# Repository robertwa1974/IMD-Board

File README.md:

# DIY insulation monitor (IMD) for EV conversions

An insulation monitoring device for DIY EV conversions. It measures the insulation resistance from
HV+ and HV- to chassis using a switched-resistor bridge, and has Bender IR155-compatible outputs
(MHS PWM + OKHS). It stacks on the contactor economizer board, or runs stand-alone with one 12-pin harness plug
(power, MHS/OKHS, optional contactor and inhibit inputs, UART): see DESIGN_NOTES "Stand-alone use".

**Status:** rev A first pass: schematic, routed 110 x 66 mm PCB (JLCPCB outputs in `hw/fab/`), firmware core host-tested. Nothing built or run on hardware yet. DIY and uncertified: not a substitute for a
certified IMD in a product.

| Path | What |
|---|---|
| `HANDOFF.md` | Requirements, measurement method, economizer interface |
| `DESIGN_NOTES.md` | Part choices, calculations, PCB rules, open items |
| `hw/` | KiCad 10 schematic generated from `hw/design.py` (`imd_schematic.pdf` to view) |
| `src/imd/`, `lib/imd_core/` | IMD board firmware (STM32G031) and its host-testable core |
| `lib/ir155_decoder/`, `src/m5dial/` | IR155 MHS decoder for an M5Dial (ESP32-S3) |
| `test/` | Host unit tests: decoder, bridge maths, state machine vs. a simulated vehicle, UART frames |
| `BENCH_TEST.md` | Bench test of the IMD firmware on a Nucleo-G031K8 with a scaled low-voltage bridge (no HV) |

```
pio run -e imd             # IMD firmware (bench: Nucleo-G031K8, upload with -t upload)
pio run -e m5dial          # decoder for the M5Dial
pio test -e native         # host tests; needs gcc/g++ on PATH, e.g. MSYS2:
                           #   PATH=/c/msys64/mingw64/bin:$PATH pio test -e native
```

MIT licensed. See `LICENSE`.

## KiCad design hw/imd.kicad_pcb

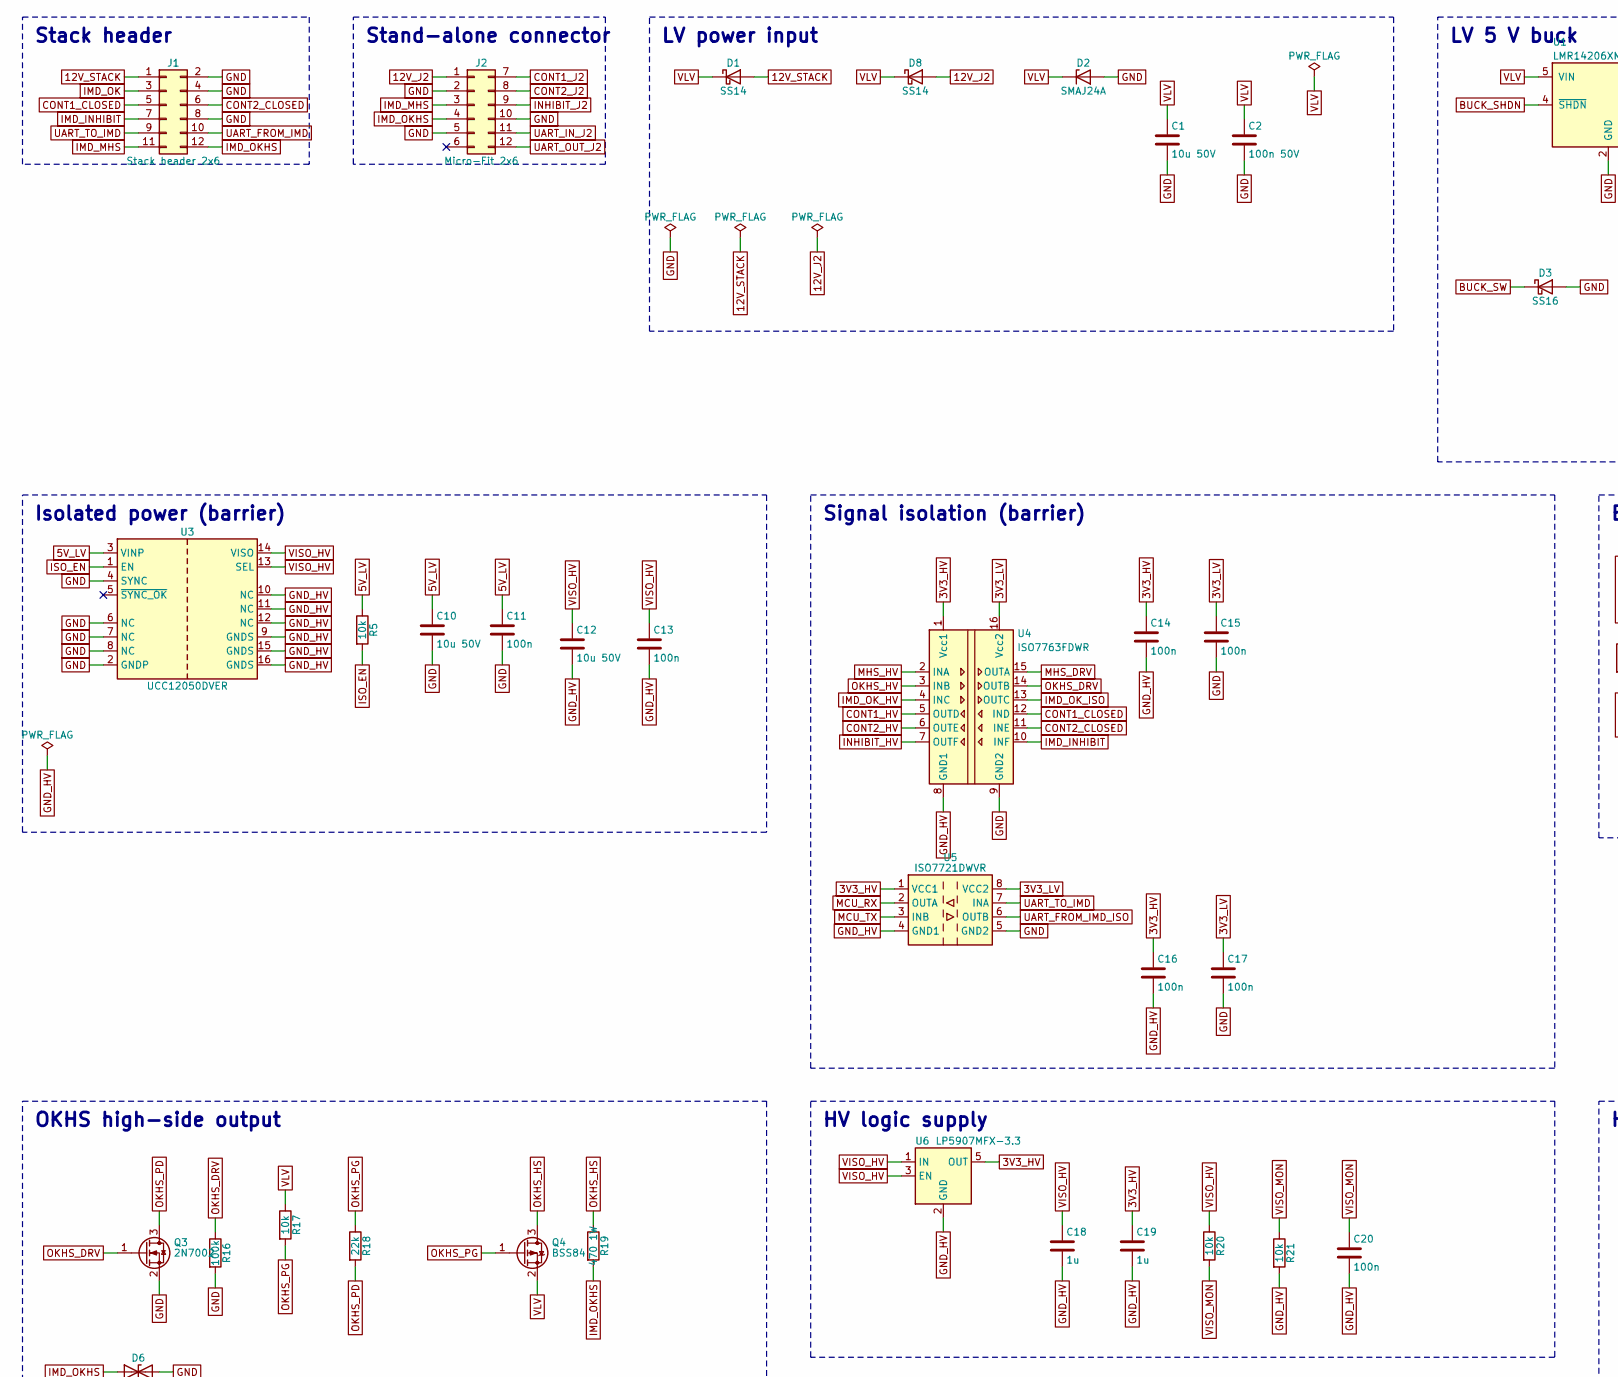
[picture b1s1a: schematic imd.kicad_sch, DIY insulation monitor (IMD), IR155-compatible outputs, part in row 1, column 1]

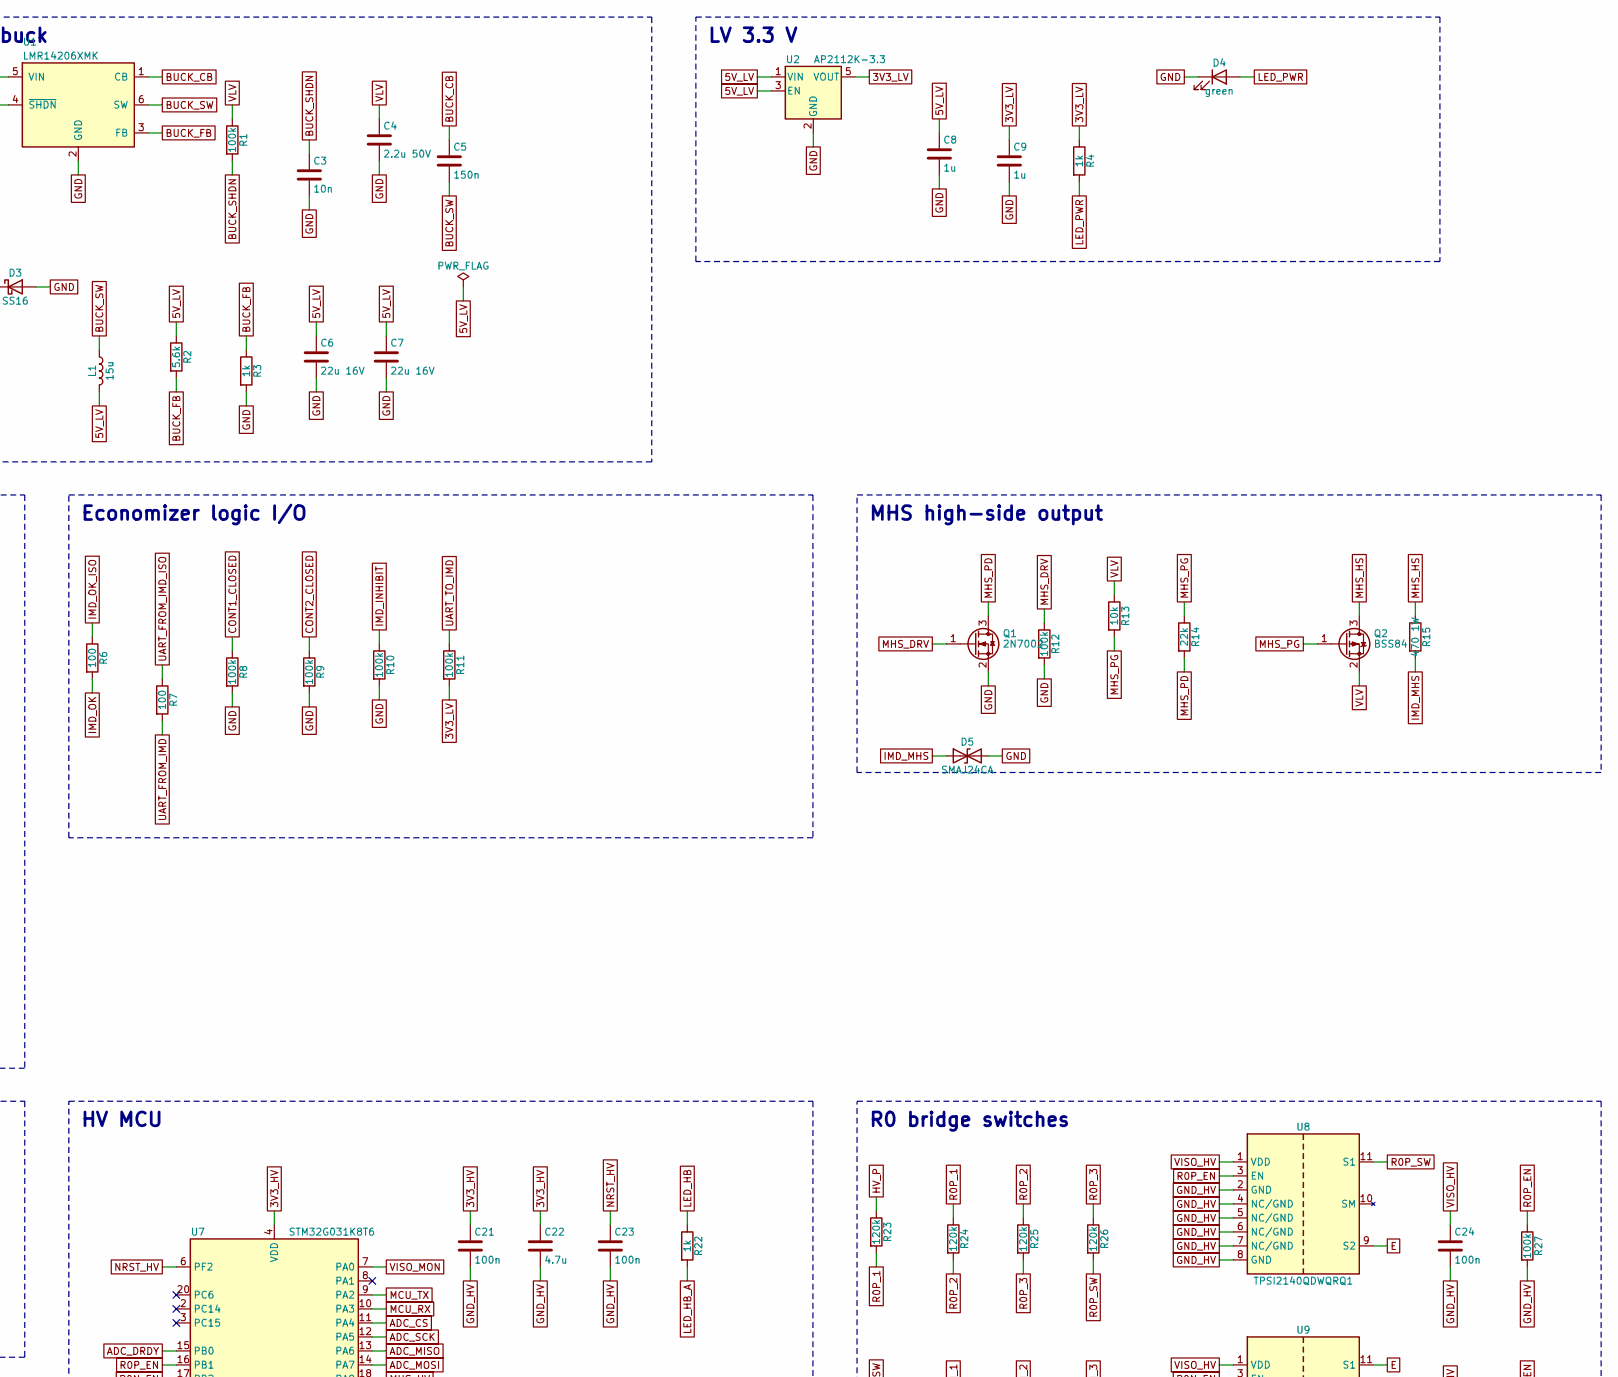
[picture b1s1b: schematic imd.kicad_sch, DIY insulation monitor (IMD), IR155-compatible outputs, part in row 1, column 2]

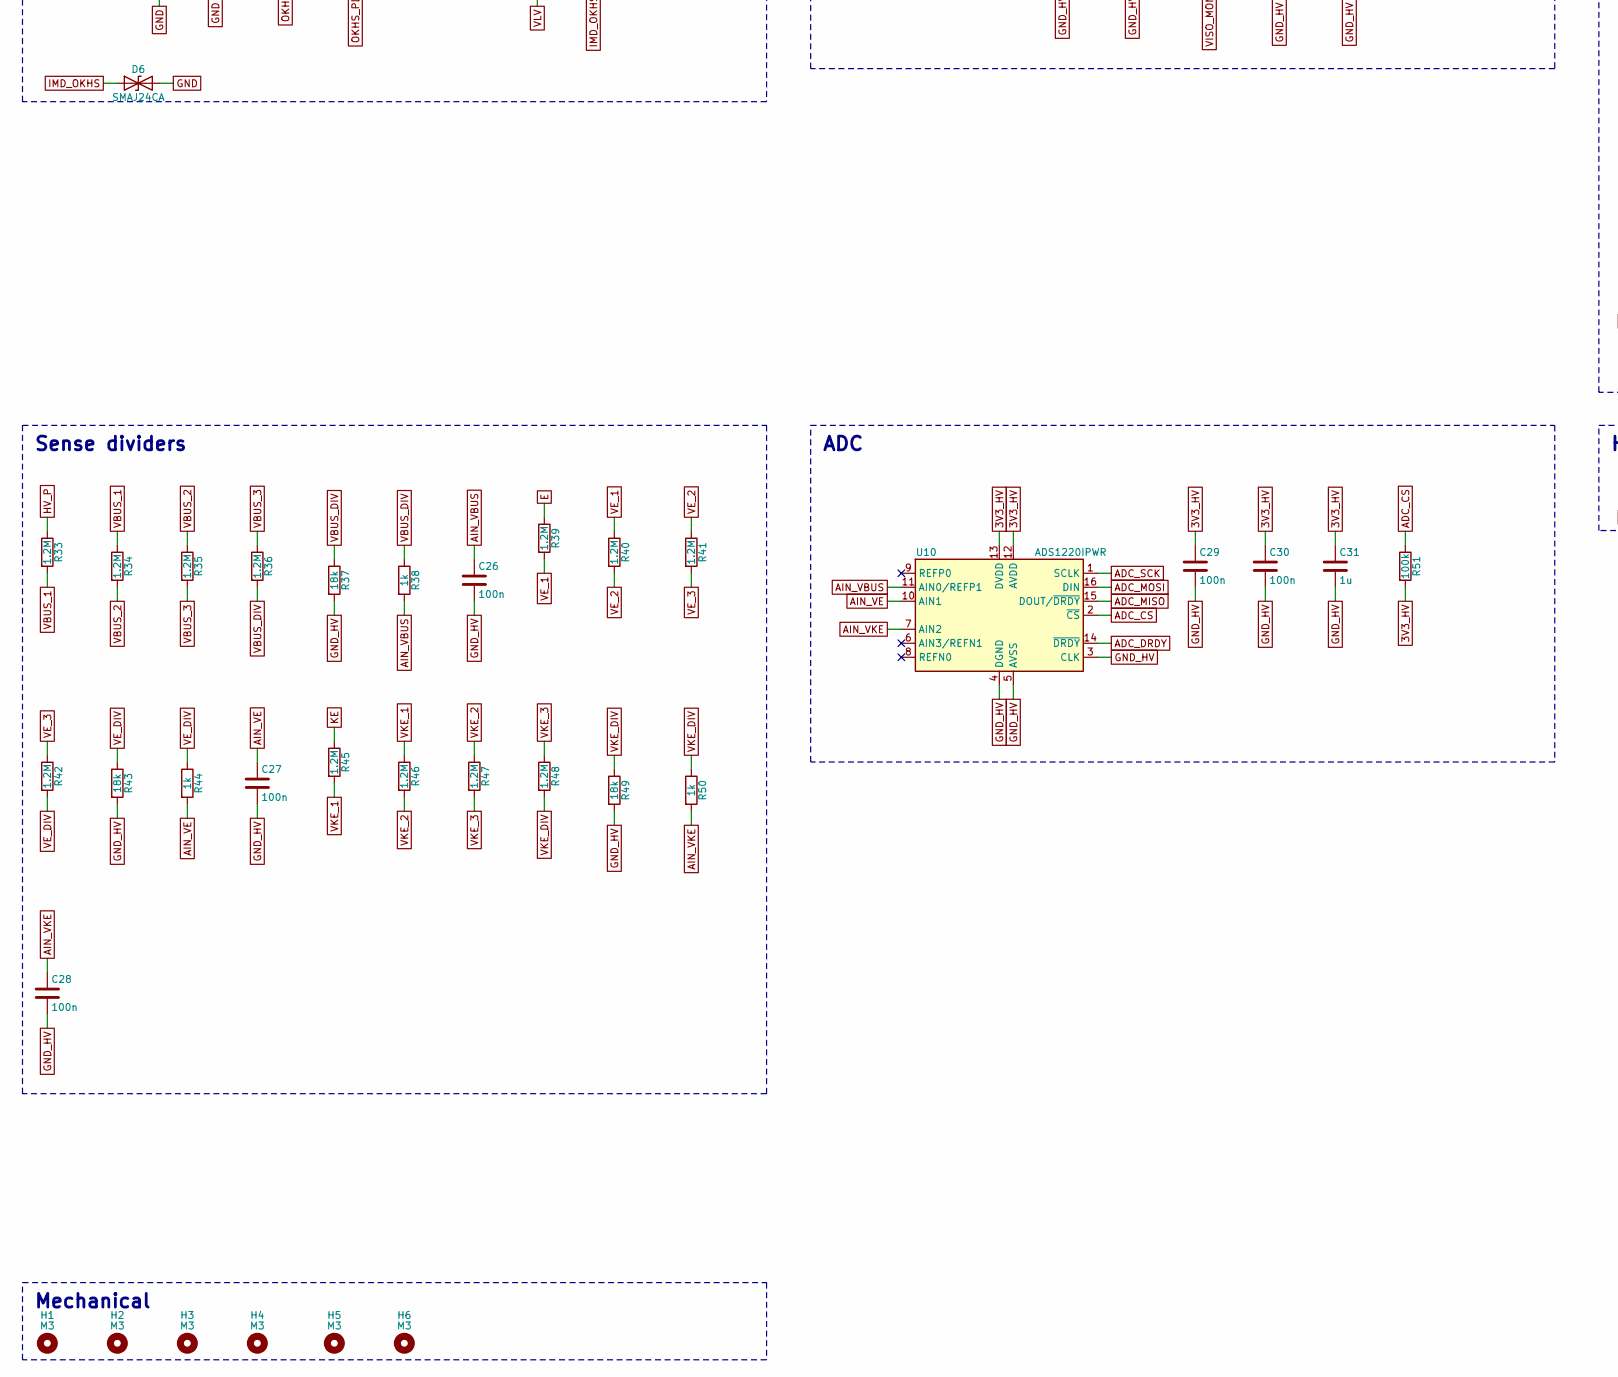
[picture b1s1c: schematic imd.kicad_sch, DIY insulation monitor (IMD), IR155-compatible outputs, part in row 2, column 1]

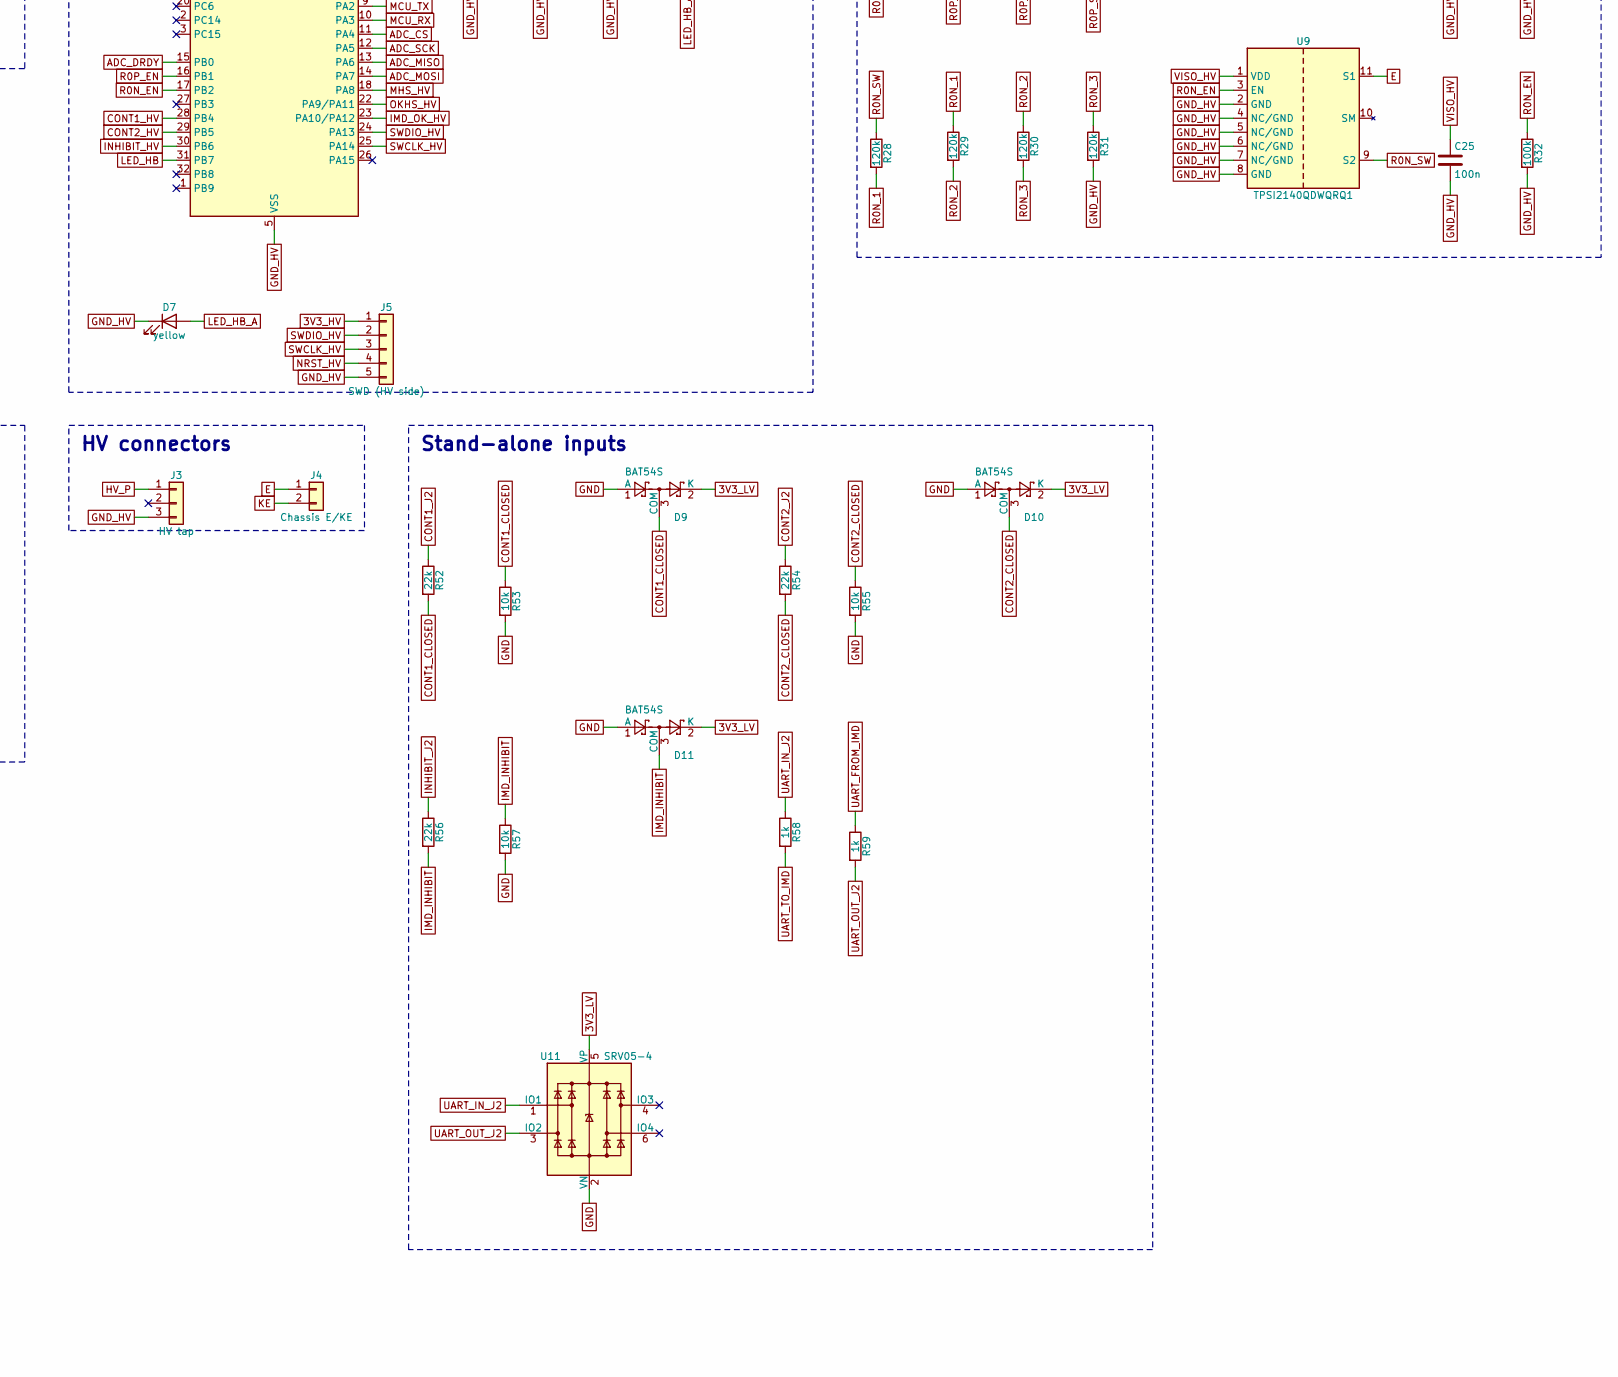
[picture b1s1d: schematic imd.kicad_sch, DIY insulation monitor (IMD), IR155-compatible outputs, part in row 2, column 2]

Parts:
C1, C10, C12: 10u 50V; C_1206_3216Metric; LCSC C13585
C2: 100n 50V; C_0603_1608Metric; LCSC C14663
C3: 10n; C_0603_1608Metric; LCSC C57112
C4: 2.2u 50V; C_1206_3216Metric; LCSC C50254
C5: 150n; C_0603_1608Metric; LCSC C282674
C6, C7: 22u 16V; C_1206_3216Metric; LCSC C12891
C8, C9, C18, C19, C31: 1u; C_0603_1608Metric; LCSC C15849
C11, C13, C14, C15, C16, C17, C20, C21, C23, C24, C25, C26, C27, C28, C29, C30: 100n; C_0603_1608Metric; LCSC C14663
C22: 4.7u; C_0603_1608Metric; LCSC C19666
D1, D8: SS14; D_SMA; MPN SS14; LCSC C2480
D2: SMAJ24A; D_SMA; MPN SMAJ24A (unidirectional TVS); LCSC C3001960
D3: SS16; D_SMA; MPN SS16; LCSC C2481
D4: green; LED_0603_1608Metric; LCSC C72043
D5, D6: SMAJ24CA; D_SMA; MPN SMAJ24CA (bidirectional); LCSC C113963
D7: yellow; LED_0603_1608Metric; LCSC C72038
D9, D10, D11: BAT54S; SOT-23; MPN BAT54S; LCSC C171786
H1, H2, H3, H4, H5, H6: M3; MountingHole_3.2mm_M3
J1: Stack header 2x6; PinHeader_2x06_P2.54mm_Vertical; MPN 2x6 elevated male header, 2.54 mm (leng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
J2: Micro-Fit 2x6; Molex_Micro-Fit_3.0_43045-1200_2x06_P3.00mm_Horizontal; MPN Molex 43045-1200; LCSC C277636
J3: HV tap; Molex_Micro-Fit_3.0_43650-0300_1x03_P3.00mm_Horizontal; MPN Molex 43650-0300; LCSC C503478
J4: Chassis E/KE; Molex_Micro-Fit_3.0_43650-0200_1x02_P3.00mm_Horizontal; MPN Molex 43650-0200 (not at LCSC: Digi-Key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
J5: SWD (HV side); PinHeader_1x05_P2.54mm_Vertical
L1: 15u; L_Bourns_SRN6045TA; MPN Bourns SRN6045-150M; LCSC C3224592
Q1, Q3: 2N7002; SOT-23; MPN 2N7002; LCSC C8545
Q2, Q4: BSS84; SOT-23; MPN LBSS84LT1G; LCSC C8492
R1, R8, R9, R10, R11, R12, R16, R27, R32, R51: 100k; R_0603_1608Metric; LCSC C25803
R2: 5.6k; R_0603_1608Metric; LCSC C23189
R3, R4, R22, R38, R44, R50, R58, R59: 1k; R_0603_1608Metric; LCSC C21190
R5, R13, R17, R20, R21, R53, R55, R57: 10k; R_0603_1608Metric; LCSC C25804
R6, R7: 100; R_0603_1608Metric; LCSC C22775
R14, R18, R52, R54, R56: 22k; R_0603_1608Metric; LCSC C31850
R15, R19: 470 1W; R_2512_6332Metric; LCSC C351718
R23, R24, R25, R26, R28, R29, R30, R31: 120k; R_1206_3216Metric; MPN 1206 thick film 1 %, 200 V rated (112 V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; LCSC C17908
R33, R34, R35, R36, R39, R40, R41, R42, R45, R46, R47, R48: 1.2M; R_1206_3216Metric; MPN 1206 thick film 1 %, 200 V rated (112 V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; LCSC C22107
R37, R43, R49: 18k; R_0603_1608Metric; LCSC C25810
U1: LMR14206XMK; TSOT-23-6; MPN LMR14206XMKE/NOPB; LCSC C2071127
U2: AP2112K-3.3; SOT-23-5; MPN AP2112K-3.3TRG1; LCSC C51118
U3: UCC12050DVER; SOIC-16W_7.5x10.3mm_P1.27mm; MPN UCC12050DVER (UCC12051QDVERQ1 automotiv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; LCSC C504571
U4: ISO7763FDWR; SOIC-16W_7.5x10.3mm_P1.27mm; MPN ISO7763FDWR; LCSC C2871771
U5: ISO7721DWVR; SOIC-8_7.5x5.85mm_P1.27mm; MPN ISO7721DWVR; LCSC C2864013
U6: LP5907MFX-3.3; SOT-23-5; MPN LP5907MFX-3.3/NOPB; LCSC C80670
U7: STM32G031K8T6; LQFP-32_7x7mm_P0.8mm; MPN STM32G031K8T6; LCSC C432203
U8, U9: TPSI2140QDWQRQ1; TI_DWQ0011A_SOIC-11_HV; MPN TPSI2140QDWQRQ1; LCSC C19089118
U10: ADS1220IPWR; TSSOP-16_4.4x5mm_P0.65mm; MPN ADS1220IPWR; LCSC C48263
U11: SRV05-4; SOT-23-6; MPN SRV05-4 (MSKSEMI); LCSC C2836319

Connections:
3V3_HV: C14.1, C16.1, C19.1, C21.1, C22.1, C29.1, C30.1, C31.1, J5.1, R51.2, U4.1 (Vcc1), U5.1 (VCC1), U6.5 (OUT), U7.4 (VDD), U10.12 (AVDD), U10.13 (DVDD)
3V3_LV: C9.1, C15.1, C17.1, D9.2 (K), D10.2 (K), D11.2 (K), R4.1, R11.2, U2.5 (VOUT), U4.16 (Vcc2), U5.8 (VCC2), U11.5 (VP)
5V_LV: C6.1, C7.1, C8.1, C10.1, C11.1, L1.2, R2.1, R5.1, U2.1 (VIN), U2.3 (EN), U3.3 (VINP)
12V_J2: D8.2 (A), J2.1
12V_STACK: D1.2 (A), J1.1
ADC_CS: R51.1, U7.11 (PA4), U10.2 (~CS)
ADC_DRDY: U7.15 (PB0), U10.14 (~DRDY)
ADC_MISO: U7.13 (PA6), U10.15 (DOUT/~DRDY)
ADC_MOSI: U7.14 (PA7), U10.16 (DIN)
ADC_SCK: U7.12 (PA5), U10.1 (SCLK)
AIN_VBUS: C26.1, R38.2, U10.11 (AIN0/REFP1)
AIN_VE: C27.1, R44.2, U10.10 (AIN1)
AIN_VKE: C28.1, R50.2, U10.7 (AIN2)
BUCK_CB: C5.1, U1.1 (CB)
BUCK_FB: R2.2, R3.1, U1.3 (FB)
BUCK_SHDN: C3.1, R1.2, U1.4 (~SHDN)
BUCK_SW: C5.2, D3.1 (K), L1.1, U1.6 (SW)
CONT1_CLOSED: D9.3 (COM), J1.5, R8.1, R52.2, R53.1, U4.12 (IND)
CONT1_HV: U4.5 (OUTD), U7.28 (PB4)
CONT1_J2: J2.7, R52.1
CONT2_CLOSED: D10.3 (COM), J1.6, R9.1, R54.2, R55.1, U4.11 (INE)
CONT2_HV: U4.6 (OUTE), U7.29 (PB5)
CONT2_J2: J2.8, R54.1
E: J4.1, R39.1, U8.9 (S2), U9.11 (S1)
GND: C1.2, C2.2, C3.2, C4.2, C6.2, C7.2, C8.2, C9.2, C10.2, C11.2, C15.2, C17.2, D2.2 (A), D3.2 (A), D4.1 (K), D5.2 (A2), D6.2 (A2), D9.1 (A), D10.1 (A), D11.1 (A), J1.2, J1.4, J1.8, J2.2, J2.5, J2.10, Q1.2 (S), Q3.2 (S), R3.2, R8.2, R9.2, R10.2, R12.2, R16.2, R53.2, R55.2, R57.2, U1.2 (GND), U2.2 (GND), U3.2 (GNDP), U3.4 (SYNC), U3.6 (NC), U3.7 (NC), U3.8 (NC), U4.9 (GND2), U5.5 (GND2), U11.2 (VN)
GND_HV: C12.2, C13.2, C14.2, C16.2, C18.2, C19.2, C20.2, C21.2, C22.2, C23.2, C24.2, C25.2, C26.2, C27.2, C28.2, C29.2, C30.2, C31.2, D7.1 (K), J3.3, J5.5, R21.2, R27.2, R31.2, R32.2, R37.2, R43.2, R49.2, U3.9 (GNDS), U3.10 (NC), U3.11 (NC), U3.12 (NC), U3.15 (GNDS), U3.16 (GNDS), U4.8 (GND1), U5.4 (GND1), U6.2 (GND), U7.5 (VSS), U8.2 (GND), U8.4 (NC/GND), U8.5 (NC/GND), U8.6 (NC/GND), U8.7 (NC/GND), U8.8 (GND), U9.2 (GND), U9.4 (NC/GND), U9.5 (NC/GND), U9.6 (NC/GND), U9.7 (NC/GND), U9.8 (GND), U10.3 (CLK), U10.4 (DGND), U10.5 (AVSS)
HV_P: J3.1, R23.1, R33.1
IMD_INHIBIT: D11.3 (COM), J1.7, R10.1, R56.2, R57.1, U4.10 (INF)
IMD_MHS: D5.1 (A1), J1.11, J2.3, R15.2
IMD_OK: J1.3, R6.2
IMD_OKHS: D6.1 (A1), J1.12, J2.4, R19.2
IMD_OK_HV: U4.4 (INC), U7.23 (PA10/PA12)
IMD_OK_ISO: R6.1, U4.13 (OUTC)
INHIBIT_HV: U4.7 (OUTF), U7.30 (PB6)
INHIBIT_J2: J2.9, R56.1
ISO_EN: R5.2, U3.1 (EN)
KE: J4.2, R45.1
LED_HB: R22.1, U7.31 (PB7)
LED_HB_A: D7.2 (A), R22.2
LED_PWR: D4.2 (A), R4.2
MCU_RX: U5.2 (OUTA), U7.10 (PA3)
MCU_TX: U5.3 (INB), U7.9 (PA2)
MHS_DRV: Q1.1 (G), R12.1, U4.15 (OUTA)
MHS_HS: Q2.3 (D), R15.1
MHS_HV: U4.2 (INA), U7.18 (PA8)
MHS_PD: Q1.3 (D), R14.2
MHS_PG: Q2.1 (G), R13.2, R14.1
NRST_HV: C23.1, J5.4, U7.6 (PF2)
OKHS_DRV: Q3.1 (G), R16.1, U4.14 (OUTB)
OKHS_HS: Q4.3 (D), R19.1
OKHS_HV: U4.3 (INB), U7.22 (PA9/PA11)
OKHS_PD: Q3.3 (D), R18.2
OKHS_PG: Q4.1 (G), R17.2, R18.1
R0N_1: R28.2, R29.1
R0N_2: R29.2, R30.1
R0N_3: R30.2, R31.1
R0N_EN: R32.1, U7.17 (PB2), U9.3 (EN)
R0N_SW: R28.1, U9.9 (S2)
R0P_1: R23.2, R24.1
R0P_2: R24.2, R25.1
R0P_3: R25.2, R26.1
R0P_EN: R27.1, U7.16 (PB1), U8.3 (EN)
R0P_SW: R26.2, U8.11 (S1)
SWCLK_HV: J5.3, U7.25 (PA14)
SWDIO_HV: J5.2, U7.24 (PA13)
UART_FROM_IMD: J1.10, R7.2, R59.1
UART_FROM_IMD_ISO: R7.1, U5.6 (OUTB)
UART_IN_J2: J2.11, R58.1, U11.1 (IO1)
UART_OUT_J2: J2.12, R59.2, U11.3 (IO2)
UART_TO_IMD: J1.9, R11.1, R58.2, U5.7 (INA)
VBUS_1: R33.2, R34.1
VBUS_2: R34.2, R35.1
VBUS_3: R35.2, R36.1
VBUS_DIV: R36.2, R37.1, R38.1
VE_1: R39.2, R40.1
VE_2: R40.2, R41.1
VE_3: R41.2, R42.1
VE_DIV: R42.2, R43.1, R44.1
VISO_HV: C12.1, C13.1, C18.1, C24.1, C25.1, R20.1, U3.13 (SEL), U3.14 (VISO), U6.1 (IN), U6.3 (EN), U8.1 (VDD), U9.1 (VDD)
VISO_MON: C20.1, R20.2, R21.1, U7.7 (PA0)
VKE_1: R45.2, R46.1
VKE_2: R46.2, R47.1
VKE_3: R47.2, R48.1
VKE_DIV: R48.2, R49.1, R50.1
VLV: C1.1, C2.1, C4.1, D1.1 (K), D2.1 (K), D8.1 (K), Q2.2 (S), Q4.2 (S), R1.1, R13.1, R17.1, U1.5 (VIN)

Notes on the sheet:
Stack header
Stand-alone connector
LV power input
LV 5 V buck
LV 3.3 V
Isolated power (barrier)
Signal isolation (barrier)
Economizer logic I/O
MHS high-side output
OKHS high-side output
HV logic supply
HV MCU
R0 bridge switches
Sense dividers
ADC
HV connectors
Stand-alone inputs
Mechanical

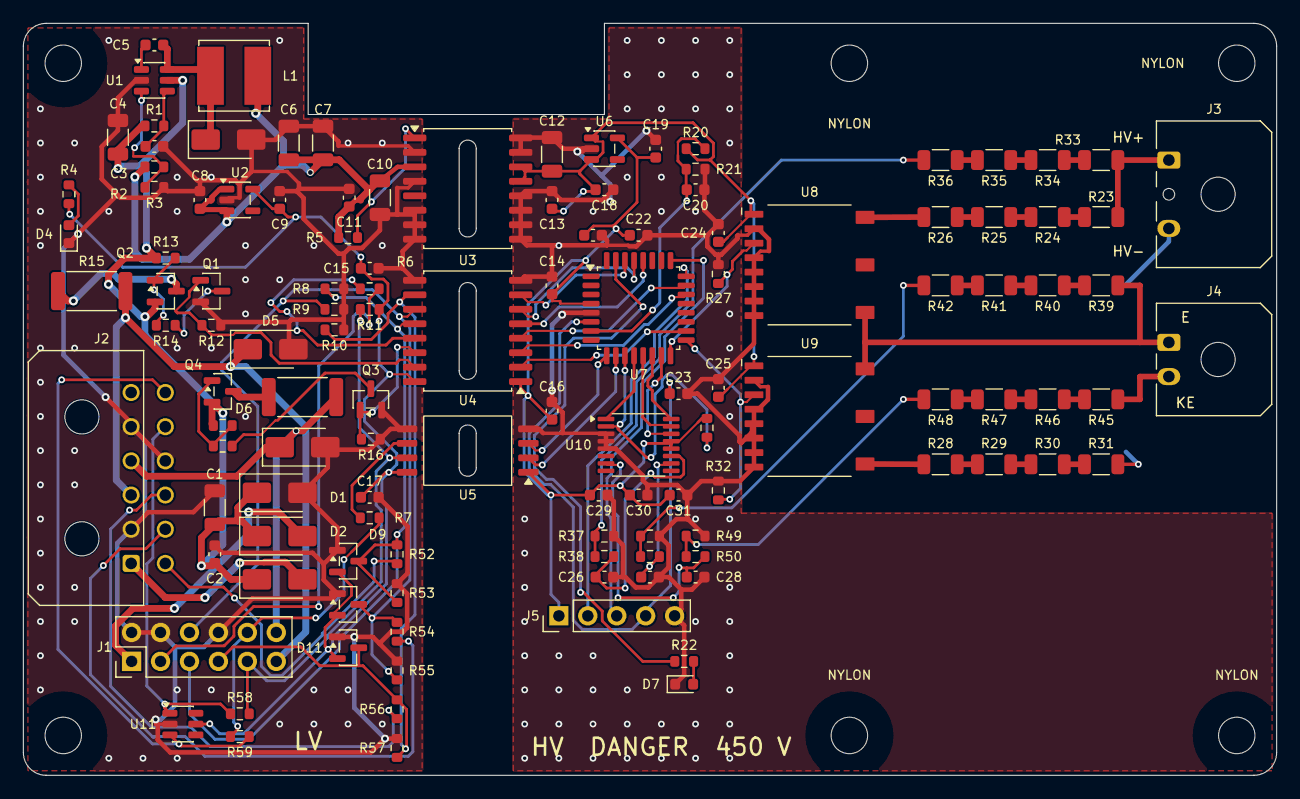
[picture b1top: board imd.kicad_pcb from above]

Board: 2 copper layers, 110.0 x 66.0 mm, 128 parts (0 on the bottom side), 85 nets.

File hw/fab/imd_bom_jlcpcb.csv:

Comment,Designator,Footprint,LCSC Part #,MPN,Qty,Notes
Stack header 2x6,J1,PinHeader_2x06_P2.54mm_Vertical,,"2x6 elevated male header, 2.54 mm (length to suit 15 mm standoffs + 8.5 mm socket)",1,HAND-SOLDER (not in CPL). Footprint on top side at the same XY/rotation as economizer J4; header inserted from below
Micro-Fit 2x6,J2,Molex_Micro-Fit_3.0_43045-1200_2x06_P3.00mm_Horizontal,C277636,Molex 43045-1200,1,"HAND-SOLDER (not in CPL). Stand-alone: 1 +12V, 2/5/10 GND, 3 MHS, 4 OKHS, 6 spare, 7 CONT1, 8 CONT2, 9 INHIBIT (12 V level), 11 UART into IMD, 12 UART from IMD (3.3 V)"
SS14,"D1,D8",D_SMA,C2480,SS14,2,"D1: Stack input. With D8: diode-OR, so J2 can never back-feed the economizer 12V_PROT; D8: Stand-alone input (J2), reverse polarity; diode-OR with D1"
SMAJ24A,D2,D_SMA,C3001960,SMAJ24A (unidirectional TVS),1,Load-dump clamp for stand-alone use (economizer already clamps when stacked)
10u 50V,"C1,C10,C12",C_1206_3216Metric,C13585,,3,C10: At VINP pin 3 / GNDP pin 2. 1206 50 V: keeps most of 10 uF at 5 V bias; C12: At VISO pin 14 / GNDS pin 15. 1206 50 V: keeps most of 10 uF at 5 V bias
100n 50V,C2,C_0603_1608Metric,C14663,,1,
LMR14206XMK,U1,TSOT-23-6,C2071127,LMR14206XMKE/NOPB,1,"4.5-42 V in, 1.25 MHz, 0.6 A. Values from datasheet Fig. 10 (5 V out)"
100k,"R1,R8,R9,R10,R11,R12,R16,R27,R32,R51",R_0603_1608Metric,C25803,,10,R1: Datasheet: 100k from supply when SHDN may see >42 V; R8: Stand-alone: open = not closed; R10: Stand-alone: open = measure; R11: UART idle high when no economizer; R12: Off while LV logic is unpowered; R16: Off while LV logic is unpowered; R27: Switch off during MCU reset; R32: Switch off during MCU reset; R51: ADC deselected during MCU reset
10n,C3,C_0603_1608Metric,C57112,,1,Soft start
2.2u 50V,C4,C_1206_3216Metric,C50254,,1,"CIN, at VIN/GND pins"
150n,C5,C_0603_1608Metric,C282674,,1,CBOOT >= 0.15 uF
SS16,D3,D_SMA,C2481,SS16,1,"Catch diode, 60 V 1 A (datasheet example)"
15u,L1,L_Bourns_SRN6045TA,C3224592,Bourns SRN6045-150M,1,1.9 A rated (datasheet asks >= 1.1 A); same 6x6 land as SRN6045TA
5.6k,R2,R_0603_1608Metric,C23189,,1,Vout = 0.765 V x (1 + 5.6k/1k) = 5.05 V (both JLCPCB Basic)
1k,"R3,R4,R22,R38,R44,R50,R58,R59",R_0603_1608Metric,C21190,,8,R58: Series protection; a 5 V adapter is clamped by U11; R59: Series protection
22u 16V,"C6,C7",C_1206_3216Metric,C12891,,2,
AP2112K-3.3,U2,SOT-23-5,C51118,AP2112K-3.3TRG1,1,
1u,"C8,C9,C18,C19,C31",C_0603_1608Metric,C15849,,5,
green,D4,LED_0603_1608Metric,C72043,,1,LV power
UCC12050DVER,U3,SOIC-16W_7.5x10.3mm_P1.27mm,C504571,UCC12050DVER (UCC12051QDVERQ1 automotive),1,"SEL=VISO -> 5.0 V. SYNC=GNDP (internal osc). NC 6-8 to GNDP, NC 10-12 to GNDS per datasheet"
10k,"R5,R13,R17,R20,R21,R53,R55,R57",R_0603_1608Metric,C25804,,8,"R5: EN high = on; R13: Vgs = -VLV x 10/32: -3.8 V at 12 V, -12 V at the 38 V TVS clamp; R17: Vgs = -VLV x 10/32: -3.8 V at 12 V, -12 V at the 38 V TVS clamp; R20: VISO/2 to MCU ADC: supply self-test; R53: Divider bottom (with the 100k pull-down: 9.1k); R55: Divider bottom (with the 100k pull-down: 9.1k); R57: Divider bottom (with the 100k pull-down: 9.1k)"
100n,"C11,C13,C14,C15,C16,C17,C20,C21,C23,C24,C25,C26,C27,C28,C29,C30",C_0603_1608Metric,C14663,,16,"C26: Anti-alias, ~85 Hz with the divider; C27: Anti-alias, ~85 Hz with the divider; C28: Anti-alias, ~85 Hz with the divider; C29: AVDD; C30: DVDD"
ISO7763FDWR,U4,SOIC-16W_7.5x10.3mm_P1.27mm,C2871771,ISO7763FDWR,1,"F = default-low outputs. 1500 Vrms / 2121 VDC working, 8 mm creepage"
ISO7721DWVR,U5,SOIC-8_7.5x5.85mm_P1.27mm,C2864013,ISO7721DWVR,1,Non-F: idle-high UART. 8.5 mm creepage (DWV)
100,"R6,R7",R_0603_1608Metric,C22775,,2,R6: Economizer adds 1k + ESD and a 100k pull-down
2N7002,"Q1,Q3",SOT-23,C8545,2N7002,2,
22k,"R14,R18,R52,R54,R56",R_0603_1608Metric,C31850,,5,R52: 12 V-level input: divider top; R54: 12 V-level input: divider top; R56: 12 V-level input: divider top
BSS84,"Q2,Q4",SOT-23,C8492,LBSS84LT1G,2,"High-side switch, -50 V"
470 1W,"R15,R19",R_2512_6332Metric,C351718,,2,1 W: survives a dead short (0.55 W at 16 V). High = ~9.6 V into the IR155 2.2k load
SMAJ24CA,"D5,D6",D_SMA,C113963,SMAJ24CA (bidirectional),2,"Harness ESD/transients, both polarities"
LP5907MFX-3.3,U6,SOT-23-5,C80670,LP5907MFX-3.3/NOPB,1,"Low-noise LDO: MCU, ADC and the isolator HV sides"
STM32G031K8T6,U7,LQFP-32_7x7mm_P0.8mm,C432203,STM32G031K8T6,1,Same MCU as the economizer
4.7u,C22,C_0603_1608Metric,C19666,,1,
yellow,D7,LED_0603_1608Metric,C72038,,1,HV-side heartbeat
SWD (HV side),J5,PinHeader_1x05_P2.54mm_Vertical,,,1,HAND-SOLDER (not in CPL). HV-REFERENCED. Program only with the HV connector unplugged
120k,"R23,R24,R25,R26,R28,R29,R30,R31",R_1206_3216Metric,C17908,"1206 thick film 1 %, 200 V rated (112 V per part at 450 V)",8,"R23: R0 = 480k, HV+ to chassis; R28: R0 = 480k, chassis to HV-"
TPSI2140QDWQRQ1,"U8,U9",TI_DWQ0011A_SOIC-11_HV,C19089118,TPSI2140QDWQRQ1,2,"1200 V, 130 ohm, 9 mA VDD when on. SM pin: thermal only, leave unconnected"
1.2M,"R33,R34,R35,R36,R39,R40,R41,R42,R45,R46,R47,R48",R_1206_3216Metric,C22107,"1206 thick film 1 %, 200 V rated (112 V per part at 450 V)",12,R33: Pack voltage HV+ to HV-; R39: Chassis (E) to HV-; R45: Chassis (KE) to HV-: E/KE mismatch = earth-connection fault
18k,"R37,R43,R49",R_0603_1608Metric,C25810,,3,"1 %: channel gain matching comes from a one-time firmware calibration, not part tolerance"
ADS1220IPWR,U10,TSSOP-16_4.4x5mm_P0.65mm,C48263,ADS1220IPWR,1,"24-bit, internal 2.048 V ref, PGA bypassed, single-ended vs AVSS. CLK=DGND -> internal osc. REFP0/REFN0/AIN3 floating (SBAS501D 9.1.5)"
HV tap,J3,Molex_Micro-Fit_3.0_43650-0300_1x03_P3.00mm_Horizontal,C503478,Molex 43650-0300,1,"HAND-SOLDER (not in CPL). 1 = HV+ (pack side, after pack fuse), 3 = HV-. Inline HV fuses in the harness"
Chassis E/KE,J4,Molex_Micro-Fit_3.0_43650-0200_1x02_P3.00mm_Horizontal,,Molex 43650-0200 (not at LCSC: Digi-Key/Mouser),1,HAND-SOLDER (not in CPL). Two SEPARATE wires to chassis (different studs if possible). Never link E and KE on the board
BAT54S,"D9,D10,D11",SOT-23,C171786,BAT54S,3,"Clamp to 3V3_LV / GND (load dump, ESD)"
SRV05-4,U11,SOT-23-6,C2836319,SRV05-4 (MSKSEMI),1,ESD on the J2 UART pins

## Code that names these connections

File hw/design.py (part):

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B = "Stack header"
# Pin numbers match the economizer's J4 socket (economizer hw/design.py). UART names are from
# the signal's point of view, so there is no TX/RX ambiguity:
#   pin 9  UART_TO_IMD   = economizer TX (PB6) -> IMD RX
#   pin 10 UART_FROM_IMD = IMD TX -> economizer RX (PB7)
part("J", "Connector_Generic:Conn_02x06_Odd_Even", "Stack header 2x6",
     "Connector_PinHeader_2.54mm:PinHeader_2x06_P2.54mm_Vertical",
     {1: "12V_STACK", 2: "GND", 3: "IMD_OK", 4: "GND", 5: "CONT1_CLOSED", 6: "CONT2_CLOSED",
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     mpn="LMR14206XMKE/NOPB", lcsc="C2071127", note="4.5-42 V in, 1.25 MHz, 0.6 A. Values from datasheet Fig. 10 (5 V out)")
R("100k", "VLV", "BUCK_SHDN", B, note="Datasheet: 100k from supply when SHDN may see >42 V")
C("10n", "BUCK_SHDN", "GND", B, note="Soft start")
C("2.2u 50V", "VLV", "GND", B, FP_C1206, note="CIN, at VIN/GND pins")
C("150n", "BUCK_CB", "BUCK_SW", B, note="CBOOT >= 0.15 uF")
part("D", "Diode:SS16", "SS16", FP_SMA, {1: "BUCK_SW", 2: "GND"}, B, mpn="SS16", lcsc="C2481",
     note="Catch diode, 60 V 1 A (datasheet example)")
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R("10k", "5V_LV", "ISO_EN", B, note="EN high = on")
C("10u 50V", "5V_LV", "GND", B, FP_C1206, note="At VINP pin 3 / GNDP pin 2. 1206 50 V: keeps most of 10 uF at 5 V bias")
C("100n", "5V_LV", "GND", B)
C("10u 50V", "VISO_HV", "GND_HV", B, FP_C1206, note="At VISO pin 14 / GNDS pin 15. 1206 50 V: keeps most of 10 uF at 5 V bias")
C("100n", "VISO_HV", "GND_HV", B)
part("#FLG", "power:PWR_FLAG", "PWR_FLAG", "", {1: "GND_HV"}, B, ref="#FLG04")

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B = "HV MCU"
part("U", "MCU_ST_STM32G0:STM32G031K8Tx", "STM32G031K8T6", "Package_QFP:LQFP-32_7x7mm_P0.8mm",
     {4: "3V3_HV", 5: "GND_HV", 6: "NRST_HV",
      7: "VISO_MON",                       # PA0  ADC_IN0
      9: "MCU_TX", 10: "MCU_RX",           # PA2/PA3 USART2 (AF1)
      11: "ADC_CS", 12: "ADC_SCK", 13: "ADC_MISO", 14: "ADC_MOSI",   # PA4 GPIO, PA5-7 SPI1 (AF0)
      15: "ADC_DRDY",                      # PB0 EXTI
      16: "R0P_EN", 17: "R0N_EN",          # PB1, PB2
      18: "MHS_HV",                        # PA8  TIM1_CH1 (AF2) PWM
      22: "OKHS_HV", 23: "IMD_OK_HV",      # PA11, PA12
      28: "CONT1_HV", 29: "CONT2_HV", 30: "INHIBIT_HV",   # PB4, PB5, PB6
      31: "LED_HB",                        # PB7 heartbeat
      24: "SWDIO_HV", 25: "SWCLK_HV",
      1: None, 2: None, 3: None, 8: None, 20: None, 26: None, 27: None, 32: None},
     B, mpn="STM32G031K8T6", lcsc="C432203", note="Same MCU as the economizer")
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
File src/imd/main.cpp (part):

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// MHS PWM, OKHS / IMD_OK. The independent watchdog resets the MCU if the loop stalls; reset
// releases every output low.
//
// UART (PA2/PA3, through the ISO7721 to the stacking header; on a Nucleo: the ST-Link USB port):
//   every 500 ms  "$IMD,..." status frame for the economizer (lib/imd_core/imd_proto.h)
//   every 1 s     "# IMD ..." human status line (LOG OFF to silence it)
//   replies       plain text
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#include "imd_proto.h"

namespace pins {
constexpr uint32_t VISO_MON = PA0;
constexpr uint32_t ADC_CS = PA4, ADC_SCK = PA5, ADC_MISO = PA6, ADC_MOSI = PA7, ADC_DRDY = PB0;
constexpr uint32_t R0P_EN = PB1, R0N_EN = PB2;
constexpr uint32_t MHS = PA8;  // TIM1_CH1
constexpr uint32_t OKHS = PA11, IMD_OK = PA12;
constexpr uint32_t CONT1 = PB4, CONT2 = PB5, INHIBIT = PB6;
constexpr uint32_t LED_HB = PB7;
}  // namespace pins

// Sense divider: 4 x 1.2 MOhm over 18 kOhm (all three channels identical; calibration trims it).
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
enum class Mode : uint8_t { Run, CalGain, CalBridge };

static Ads1220 adc(SPI, pins::ADC_CS, pins::ADC_DRDY);
static imd::Calibration cal;
static imd::Monitor monitor;
static imd::GainCal gainCal;
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    r0Interlock = true;
  }
  // Break before make.
  if (!p) digitalWrite(pins::R0P_EN, LOW);
  if (!n) digitalWrite(pins::R0N_EN, LOW);
  if (p) digitalWrite(pins::R0P_EN, HIGH);
  if (n) digitalWrite(pins::R0N_EN, HIGH);
}

static bool logOn = true;      // human "# IMD ..." line; the $IMD frames are always sent
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static void setOk(bool ok) {
  okDriven = ok;
  digitalWrite(pins::OKHS, ok ? HIGH : LOW);
  digitalWrite(pins::IMD_OK, ok ? HIGH : LOW);
}

// ---------------------------------------------------------------- calibration storage (flash)
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// ---------------------------------------------------------------- setup / loop

static float readViso() {
  return analogRead(pins::VISO_MON) * (3.3f / 4095.0f) * 2.0f;  // 10k/10k divider
}

void setup() {
  // Everything off first: switches open, outputs "not OK".
  pinMode(pins::R0P_EN, OUTPUT);
  pinMode(pins::R0N_EN, OUTPUT);
  setR0(false, false);
  pinMode(pins::OKHS, OUTPUT);
  pinMode(pins::IMD_OK, OUTPUT);
  setOk(false);
  pinMode(pins::LED_HB, OUTPUT);
  pinMode(pins::CONT1, INPUT);
  pinMode(pins::CONT2, INPUT);
  pinMode(pins::INHIBIT, INPUT);
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  loadCal();
  loadInCfg();
  restartMonitor();
  SPI.setMOSI(pins::ADC_MOSI);
  SPI.setMISO(pins::ADC_MISO);
  SPI.setSCLK(pins::ADC_SCK);
  SPI.begin();
  adcOk = adc.begin();
  Serial.printf("IMD fw start, ADS1220 %s\n", adcOk ? "ok" : "NOT RESPONDING");
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  static char bufP[12], bufN[12];
  if (millis() - tLog >= 1000) {
    tLog = millis();
    digitalWrite(pins::LED_HB, !digitalRead(pins::LED_HB));
    if (!logOn) return;
    if (mode != Mode::Run) {
      Serial.printf("# CAL %s running, Vbus=%ld\n", mode == Mode::CalGain ? "GAIN" : "BRIDGE",
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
